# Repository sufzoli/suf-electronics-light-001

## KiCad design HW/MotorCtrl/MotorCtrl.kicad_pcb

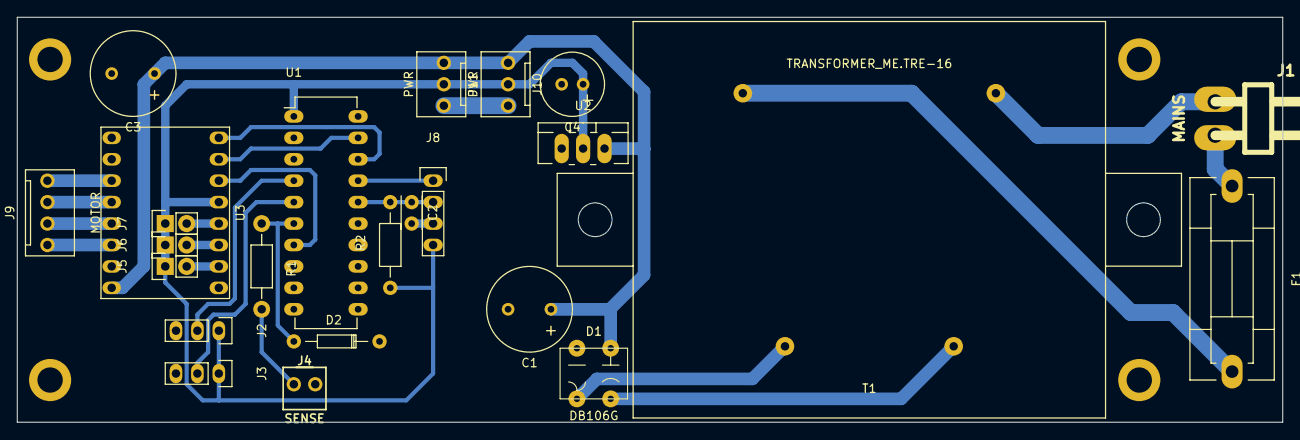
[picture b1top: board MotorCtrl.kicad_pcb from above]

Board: 2 copper layers, 150.0 x 48.0 mm, 28 parts (0 on the bottom side), 24 nets.

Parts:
C1: 1000uF/25V; Elko_vert_20x10mm_RM5
C2: C; C_Rect_L4_W2.5_P2.5
C3: 100uF/25V; Elko_vert_20x10mm_RM5
C4: 220uF/6.3V; Elko_vert_11.2x7.5mm_RM2.5
D1: DB106G; DB-4
D2: BZX55C3V3; Diode_DO-35_SOD27_Horizontal_RM10
F1: FUSE; Fuseholder5x20_horiz_SemiClosed_Casing10x25mm
J1: MAINS; CONN_NCW396-02R
J2: ENDSTOP1; Pin_Header_Straight_1x03
J3: ENDSTOP2; Pin_Header_Straight_1x03
J4: SENSE; CONN_NCW254-02S
J5, J6, J7: Pin_Header_Straight_1x02
J8: TI_SBW; Pin_Header_Straight_1x04
J9: MOTOR; CONN_NCW254-04S
J10, J11: PWR; CONN_NCW254-03S
MNT_HOLE_3.5, MNT_HOLE_3.5#2, MNT_HOLE_3.5#3, MNT_HOLE_3.5#4: Val**; MNT_HOLE_3.5
R1: 10k; Resistor_Horizontal_RM10mm
R2: 47K; Resistor_Horizontal_RM10mm
T1: TRANSFORMER_ME.TRE-16; TR_ME.TRE-16
U1: MSP430G2553; DIP-20_W7.62mm_LongPads
U2: LD1117V33; TO-220_Neutral123_Vertical_LargePads
U3: POLOLU_DRV8825; POLOLU_STEPPER

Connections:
+3V3: C4.1, J2.1, J3.1, J5.1, J6.1, J7.1, J8.4, J10.2, J11.2, R2.1, U1.1, U2.2, U3.5
+12V: C1.1, C3.1, D1.4, J10.1, J11.1, U2.3, U3.16
DIR: U1.18, U3.8
ENDSTOP1: J2.2, U1.4
ENDSTOP2: J3.2, U1.5
GND: C1.2, C2.2, C3.2, C4.2, D1.1, D2.1, J2.3, J3.3, J4.2, J8.3, J10.3, J11.3, U1.20, U2.1, U3.9, U3.15
unnamed: C2.1, J8.2, R2.2, U1.16
unnamed: D1.2, T1.13
unnamed: D1.3, T1.9
unnamed: F1.1, J1.2
unnamed: F1.2, T1.1
unnamed: J1.1, T1.7
unnamed: J4.1, R1.2
unnamed: J5.2, U3.2
unnamed: J6.2, U3.3
unnamed: J7.2, U3.4
unnamed: J8.1, U1.17
unnamed: J9.1, U3.14
unnamed: J9.2, U3.13
unnamed: J9.3, U3.12
unnamed: J9.4, U3.11
SENSE: D2.2, R1.1, U1.6
SLEEP: U1.7, U3.6
STEP: U1.19, U3.7

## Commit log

2015-09-03 Hardware design added
2021-03-20 Add remaining code - archive
